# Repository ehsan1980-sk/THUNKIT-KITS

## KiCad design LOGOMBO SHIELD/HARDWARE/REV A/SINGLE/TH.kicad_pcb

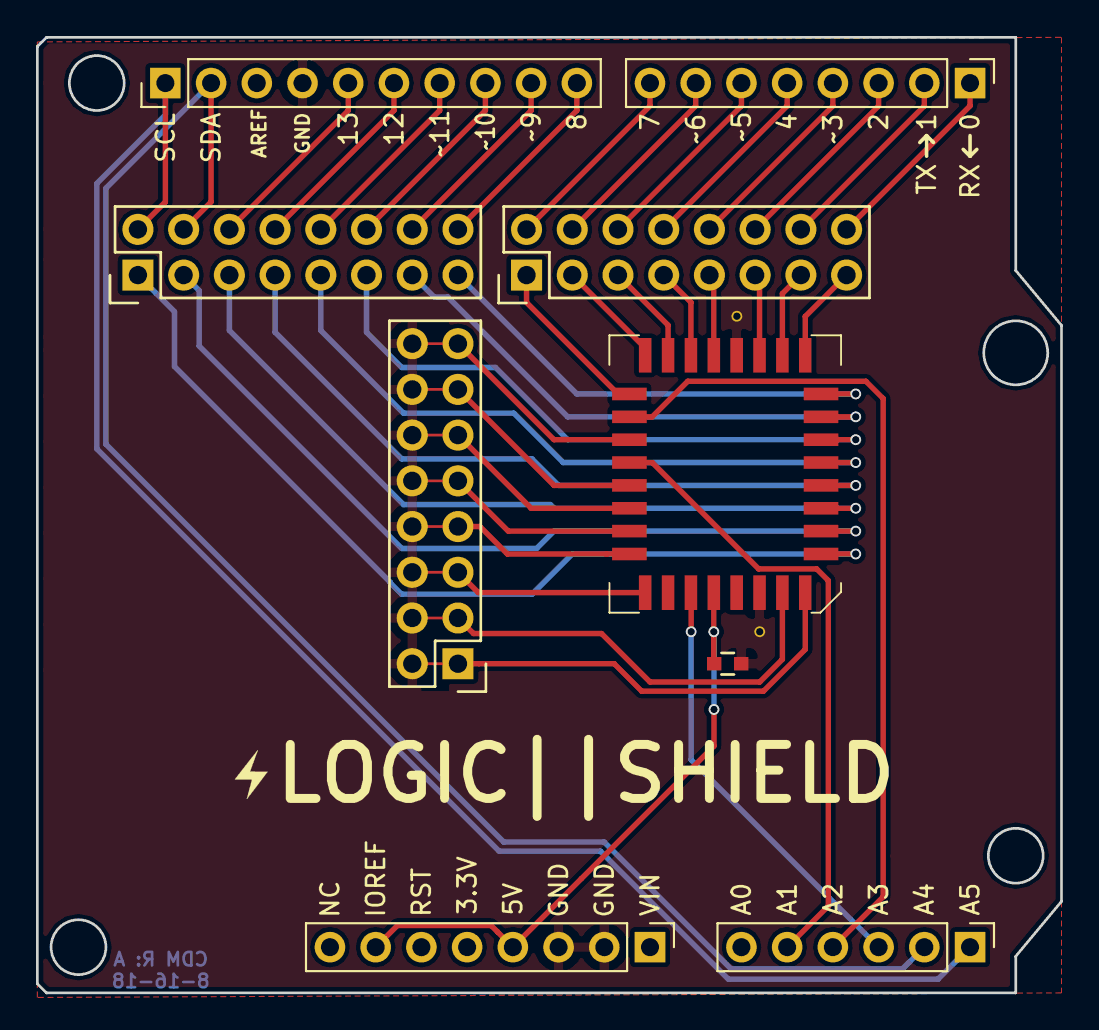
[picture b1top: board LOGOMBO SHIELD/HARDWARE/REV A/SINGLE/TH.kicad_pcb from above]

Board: 2 copper layers, 56.9 x 53.1 mm, 9 parts (0 on the bottom side), 45 nets.

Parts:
C1: 1uF; C_0603
P1, P2, P7: CONN_02X08; Pin_Header_Straight_2x08
P3, P6: CONN_01X08; Pin_Header_Straight_1x08_Pitch2.54mm
P4: CONN_01X06; Pin_Header_Straight_1x06_Pitch2.54mm
P5: CONN_01X10; Pin_Header_Straight_1x10_Pitch2.54mm
U1: SST39VF010-70-4C-NHE; PLCC-32

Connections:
+5V: C1.2, P3.4, P3.7, U1.32
GND: C1.1, P2.2, P2.4, P2.6, P2.8, P2.10, P2.12, P2.14, P2.16, P3.2, P3.3, P5.4, U1.2, U1.16
unnamed: P1.1, U1.21
unnamed: P1.3, U1.20
unnamed: P1.5, U1.19
unnamed: P1.7, U1.18
unnamed: P1.9, U1.17
unnamed: P1.11, U1.15
unnamed: P1.13, U1.14
unnamed: P1.15, U1.13
unnamed: P2.1, U1.4
unnamed: P2.3, U1.3
unnamed: P2.5, U1.29
unnamed: P2.7, U1.28
unnamed: P2.9, U1.27
unnamed: P2.11, U1.26
unnamed: P2.13, U1.25
unnamed: P2.15, U1.23
unnamed: P7.1, U1.5
unnamed: P7.3, U1.6
unnamed: P7.5, U1.7
unnamed: P7.7, U1.8
unnamed: P7.9, U1.9
unnamed: P7.11, U1.10
unnamed: P7.13, U1.11
unnamed: P7.15, U1.12
PB0: P5.10, P7.16
PB1: P5.9, P7.14
PB2: P5.8, P7.12
PB3: P5.7, P7.10
PB4: P5.6, P7.8
PB5: P5.5, P7.6
PC1: P4.5, U1.24
PC2: P4.4, U1.22
PC3: P4.3, U1.31
PC4: P4.2, P5.2, P7.4
PC5: P4.1, P5.1, P7.2
PD0: P1.16, P6.1
PD1: P1.14, P6.2
PD2: P1.12, P6.3
PD3: P1.10, P6.4
PD4: P1.8, P6.5
PD5: P1.6, P6.6
PD6: P1.4, P6.7
PD7: P1.2, P6.8

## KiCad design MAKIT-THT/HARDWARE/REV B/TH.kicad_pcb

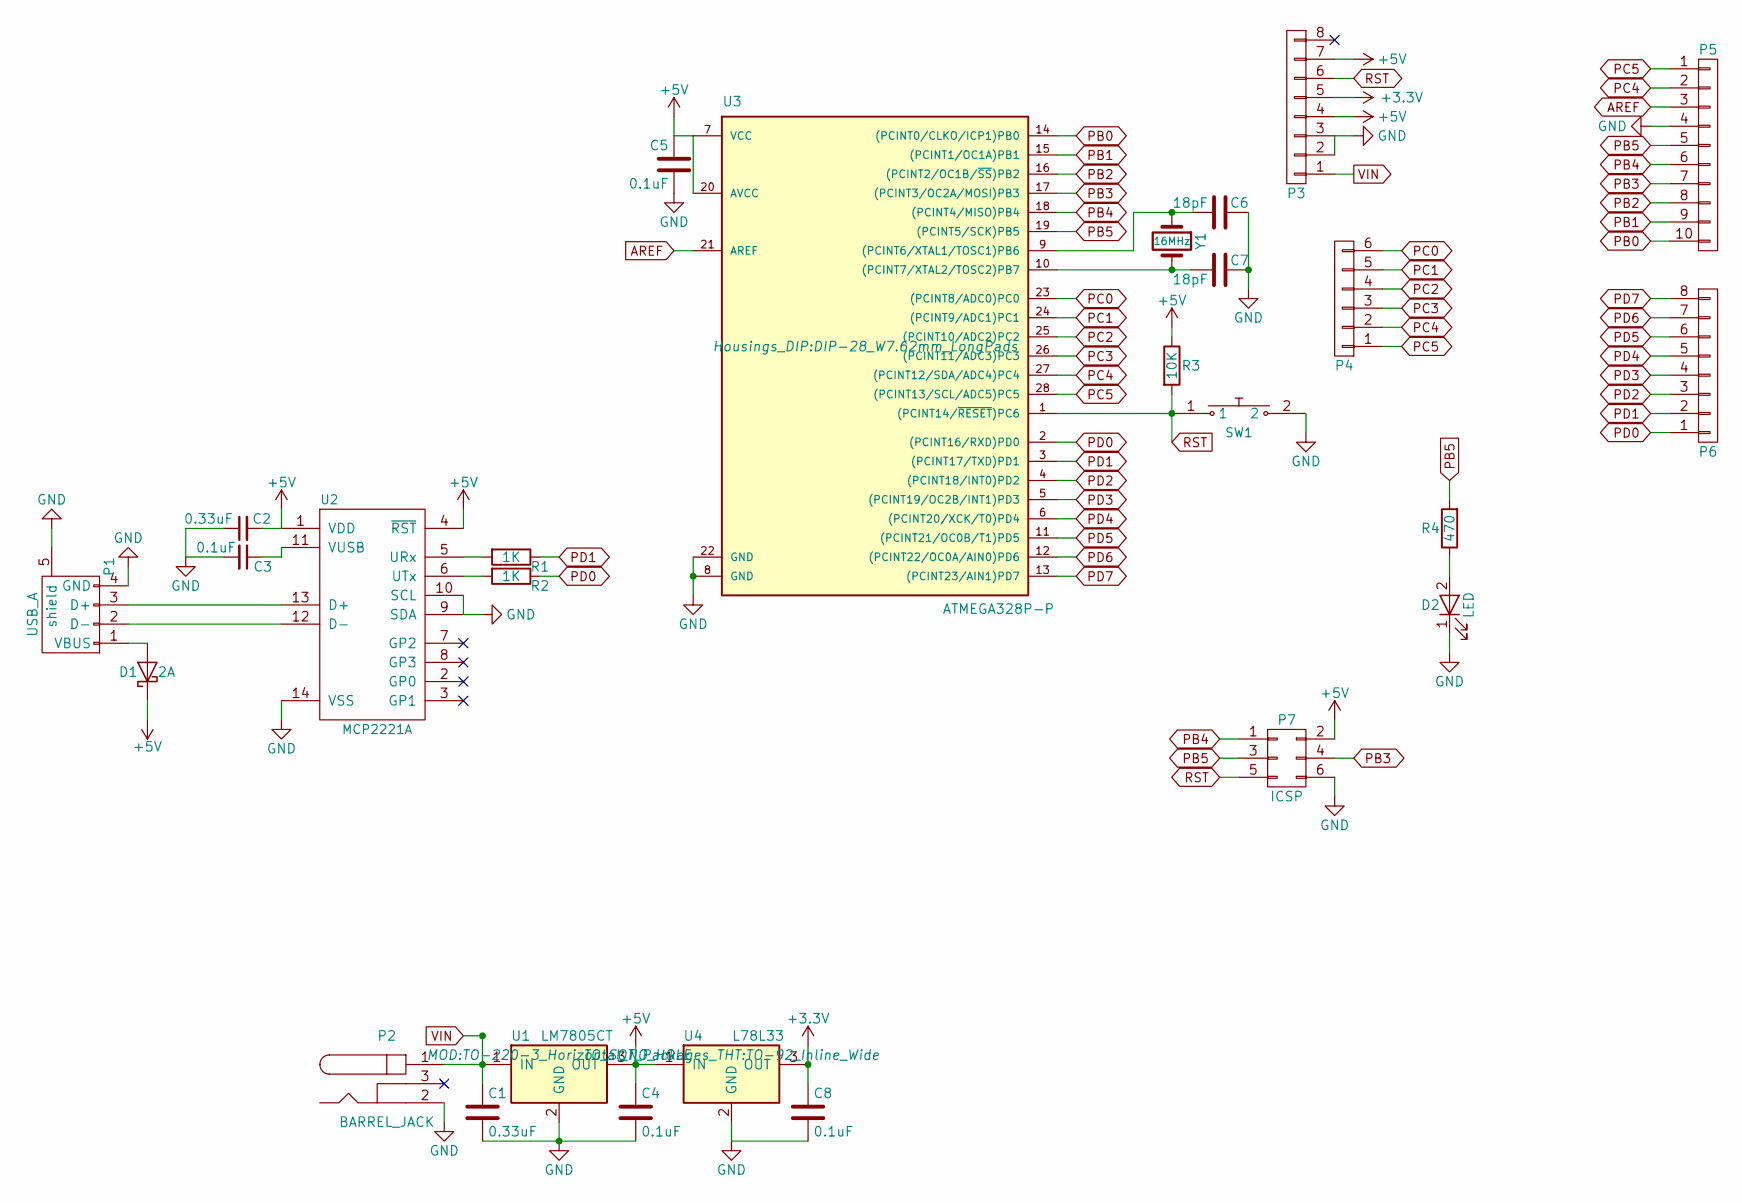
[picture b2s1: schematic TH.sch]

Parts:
C1, C2: 0.33uF; C_Disc_D3.8mm_W2.6mm_P2.50mm
C3, C4, C5, C8: 0.1uF; C_Disc_D3.8mm_W2.6mm_P2.50mm
C6, C7: 18pF; C_Disc_D3.8mm_W2.6mm_P2.50mm
D1: 2A; D_DO-15_P10.16mm_Horizontal
D2: LED; LED_D5.0mm
P1: USB_A; USB_B
P2: BARREL_JACK
P3, P6: CONN_01X08; Pin_Header_Straight_1x08_Pitch2.54mm
P4: CONN_01X06; Pin_Header_Straight_1x06_Pitch2.54mm
P5: CONN_01X10; Pin_Header_Straight_1x10_Pitch2.54mm
P7: ICSP; Pin_Header_Straight_2x03_Pitch2.54mm
R1, R2: 1K; R_Axial_DIN0207_L6.3mm_D2.5mm_P7.62mm_Horizontal
R3: 10K; R_Axial_DIN0207_L6.3mm_D2.5mm_P7.62mm_Horizontal
R4: 470; R_Axial_DIN0207_L6.3mm_D2.5mm_P7.62mm_Horizontal
SW1: Push_SW; SW_PUSH_6mm
U1: LM7805CT; TO-220-3_Horizontal_NO_HOLE
U2: MCP2221A; DIP-14_W7.62mm_LongPads
U3: ATMEGA328P-P; DIP-28_W7.62mm_LongPads
U4: L78L33; TO-92_Inline_Wide
Y1: 16MHz; Crystal_HC49-U_Vertical

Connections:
+3V3: C8.1, P3.5, U4.3 (OUT)
+5V: C2.2, C4.1, C5.1, D1.1 (K), P3.4, P3.7, P7.2, R3.1, U1.3 (OUT), U2.1 (VDD), U2.4 (~RST), U3.7 (VCC), U3.20 (AVCC), U4.1 (IN)
AREF: P5.3, U3.21 (AREF)
GND: C1.2, C2.1, C3.2, C4.2, C5.2, C6.1, C7.1, C8.2, D2.1 (K), P1.4 (GND), P1.5 (shield), P2.2, P3.2, P3.3, P5.4, P7.6, SW1.2, U1.2 (GND), U2.9 (SDA), U2.10 (SCL), U2.14 (VSS), U3.8 (GND), U3.22 (GND), U4.2 (GND)
unnamed: C3.1, U2.11 (VUSB)
unnamed: C6.2, U3.9 ((PCINT6/XTAL1/TOSC1)PB6), Y1.1
unnamed: C7.2, U3.10 ((PCINT7/XTAL2/TOSC2)PB7), Y1.2
unnamed: D1.2 (A), P1.1 (VBUS)
unnamed: D2.2 (A), R4.1
unnamed: P1.2 (D-), U2.12 (D-)
unnamed: P1.3 (D+), U2.13 (D+)
unnamed: R1.2, U2.5 (URx)
unnamed: R2.2, U2.6 (UTx)
PB0: P5.10, U3.14 ((PCINT0/CLKO/ICP1)PB0)
PB1: P5.9, U3.15 ((PCINT1/OC1A)PB1)
PB2: P5.8, U3.16 ((PCINT2/OC1B/~SS~)PB2)
PB3: P5.7, P7.4, U3.17 ((PCINT3/OC2A/MOSI)PB3)
PB4: P5.6, P7.1, U3.18 ((PCINT4/MISO)PB4)
PB5: P5.5, P7.3, R4.2, U3.19 ((PCINT5/SCK)PB5)
PC0: P4.6, U3.23 ((PCINT8/ADC0)PC0)
PC1: P4.5, U3.24 ((PCINT9/ADC1)PC1)
PC2: P4.4, U3.25 ((PCINT10/ADC2)PC2)
PC3: P4.3, U3.26 ((PCINT11/ADC3)PC3)
PC4: P4.2, P5.2, U3.27 ((PCINT12/SDA/ADC4)PC4)
PC5: P4.1, P5.1, U3.28 ((PCINT13/SCL/ADC5)PC5)
PD0: P6.1, R2.1, U3.2 ((PCINT16/RXD)PD0)
PD1: P6.2, R1.1, U3.3 ((PCINT17/TXD)PD1)
PD2: P6.3, U3.4 ((PCINT18/INT0)PD2)
PD3: P6.4, U3.5 ((PCINT19/OC2B/INT1)PD3)
PD4: P6.5, U3.6 ((PCINT20/XCK/T0)PD4)
PD5: P6.6, U3.11 ((PCINT21/OC0B/T1)PD5)
PD6: P6.7, U3.12 ((PCINT22/OC0A/AIN0)PD6)
PD7: P6.8, U3.13 ((PCINT23/AIN1)PD7)
RST: P3.6, P7.5, R3.2, SW1.1, U3.1 ((PCINT14/~RESET~)PC6)
VIN: C1.1, P2.1, P3.1, U1.1 (IN)

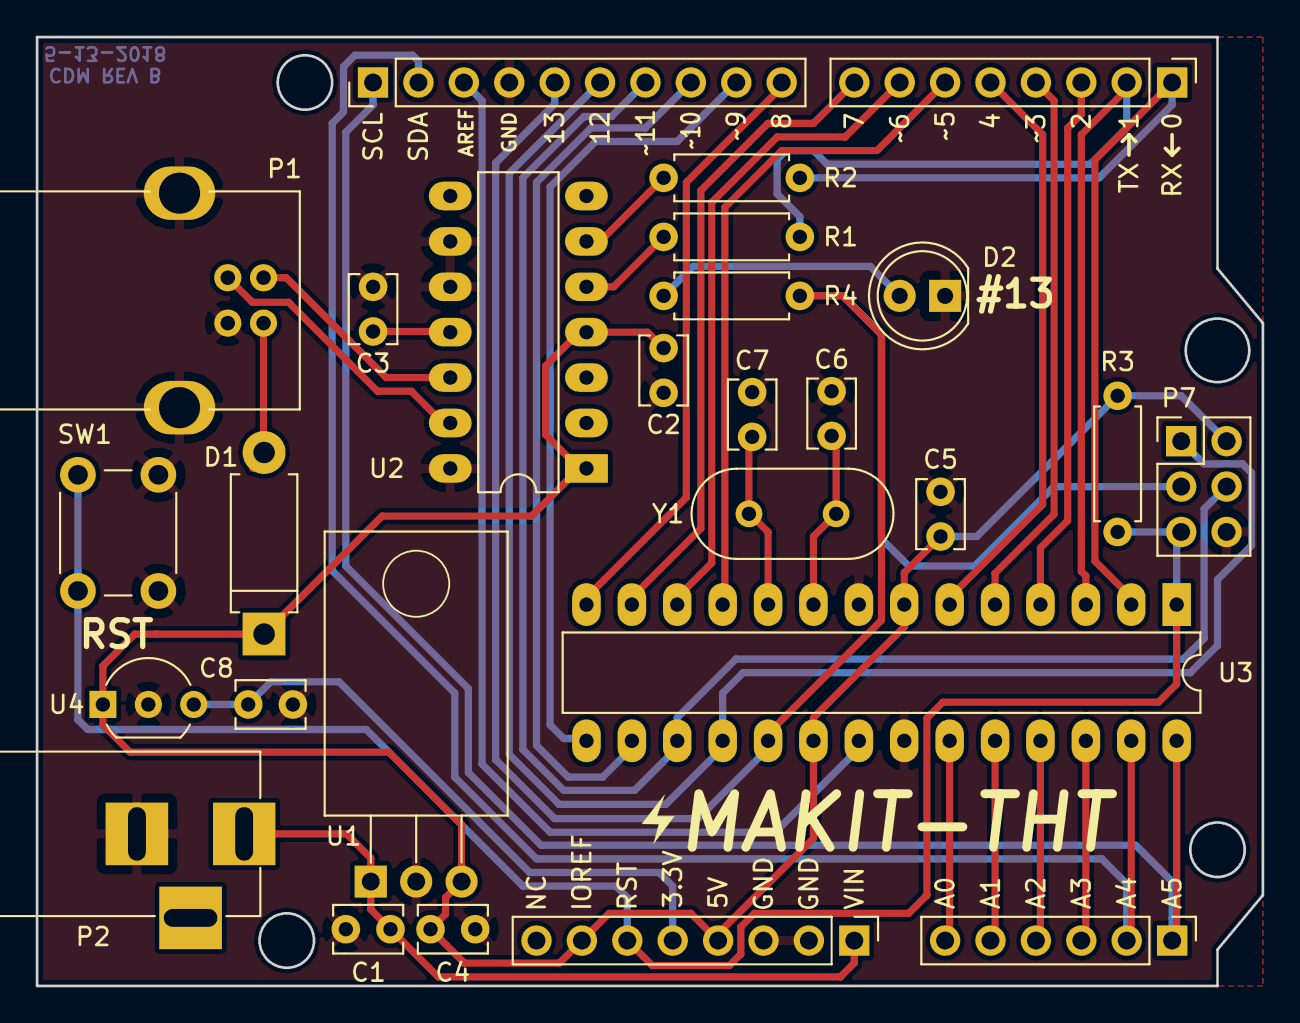
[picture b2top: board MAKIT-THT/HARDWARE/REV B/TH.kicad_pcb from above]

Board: 2 copper layers, 68.6 x 53.1 mm, 27 parts (0 on the bottom side), 35 nets.
